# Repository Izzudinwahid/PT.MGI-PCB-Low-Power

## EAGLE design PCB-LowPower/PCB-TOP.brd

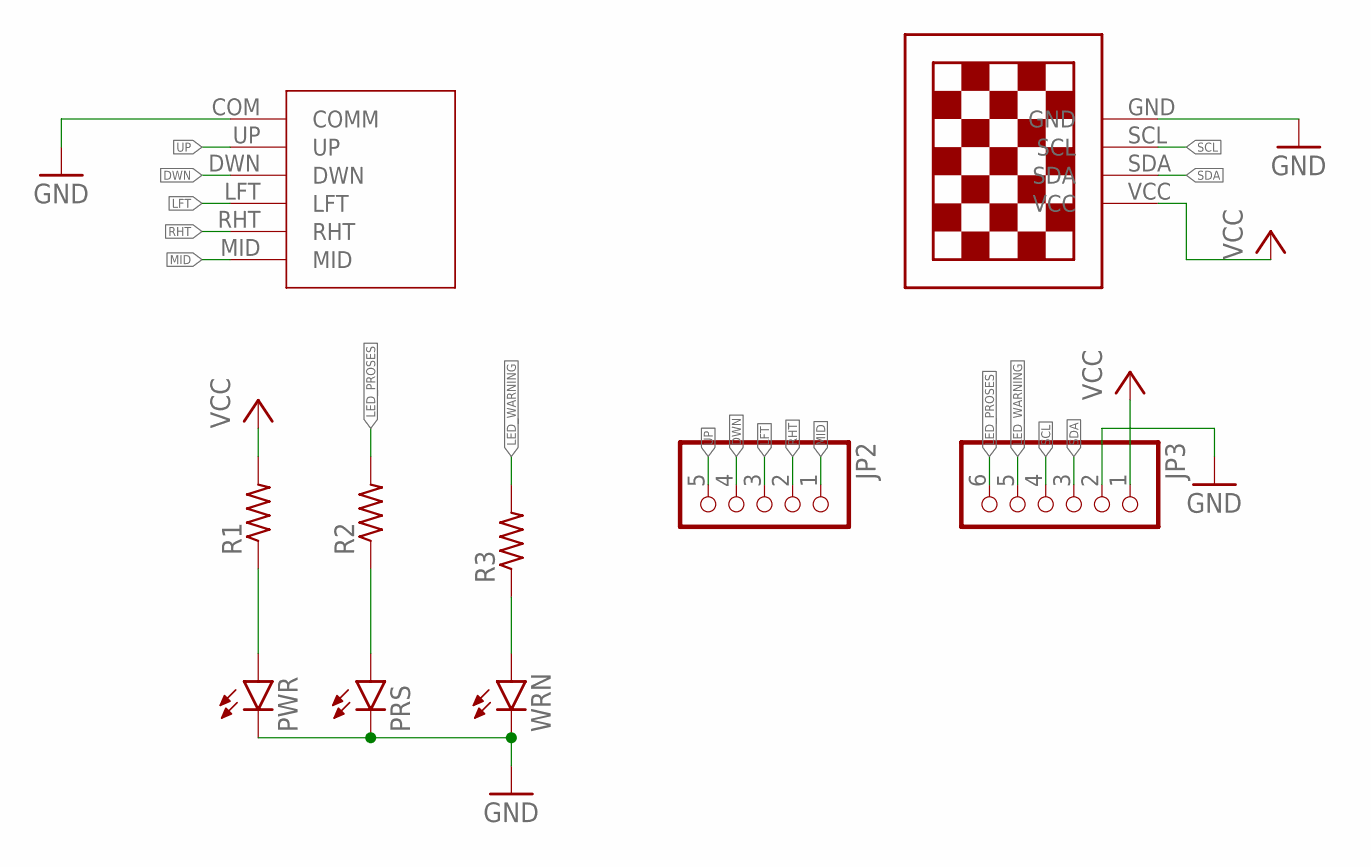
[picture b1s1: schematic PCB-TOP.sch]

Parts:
JP2: PINHD-1X5; 1X05
JP3: PINHD-1X6; 1X06
NAV-SWITCH6P1: NAV-SWITCH6P
PRS: TLLR4400; LED3MM
PWR: TLLR4400; LED3MM
R1, R2, R3: R-US_M0805; M0805
U$1: 13"OLED13"OLED; 1.3"OLED
WRN: TLLR4400; LED3MM

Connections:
DWN: JP2.4, NAV-SWITCH6P1.DWN
GND: JP3.2, NAV-SWITCH6P1.COM (COMM), PRS.K (C), PWR.K (C), U$1.GND, WRN.K (C)
LED_PROSES: JP3.6, R2.2
LED_WARNING: JP3.5, R3.2
LFT: JP2.3, NAV-SWITCH6P1.LFT
MID: JP2.1, NAV-SWITCH6P1.MID
unnamed: PWR.A, R1.1
unnamed: PRS.A, R2.1
unnamed: R3.1, WRN.A
RHT: JP2.2, NAV-SWITCH6P1.RHT
SCL: JP3.4, U$1.SCL
SDA: JP3.3, U$1.SDA
UP: JP2.5, NAV-SWITCH6P1.UP
VCC: JP3.1, R1.2, U$1.VCC

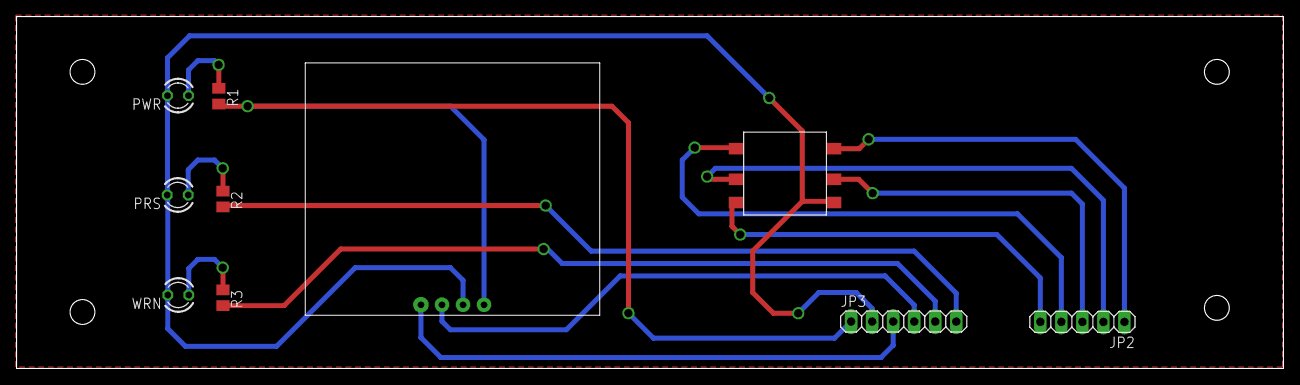
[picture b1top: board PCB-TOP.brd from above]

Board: 2 copper layers, 153.0 x 42.5 mm, 10 parts (0 on the bottom side), 14 nets.

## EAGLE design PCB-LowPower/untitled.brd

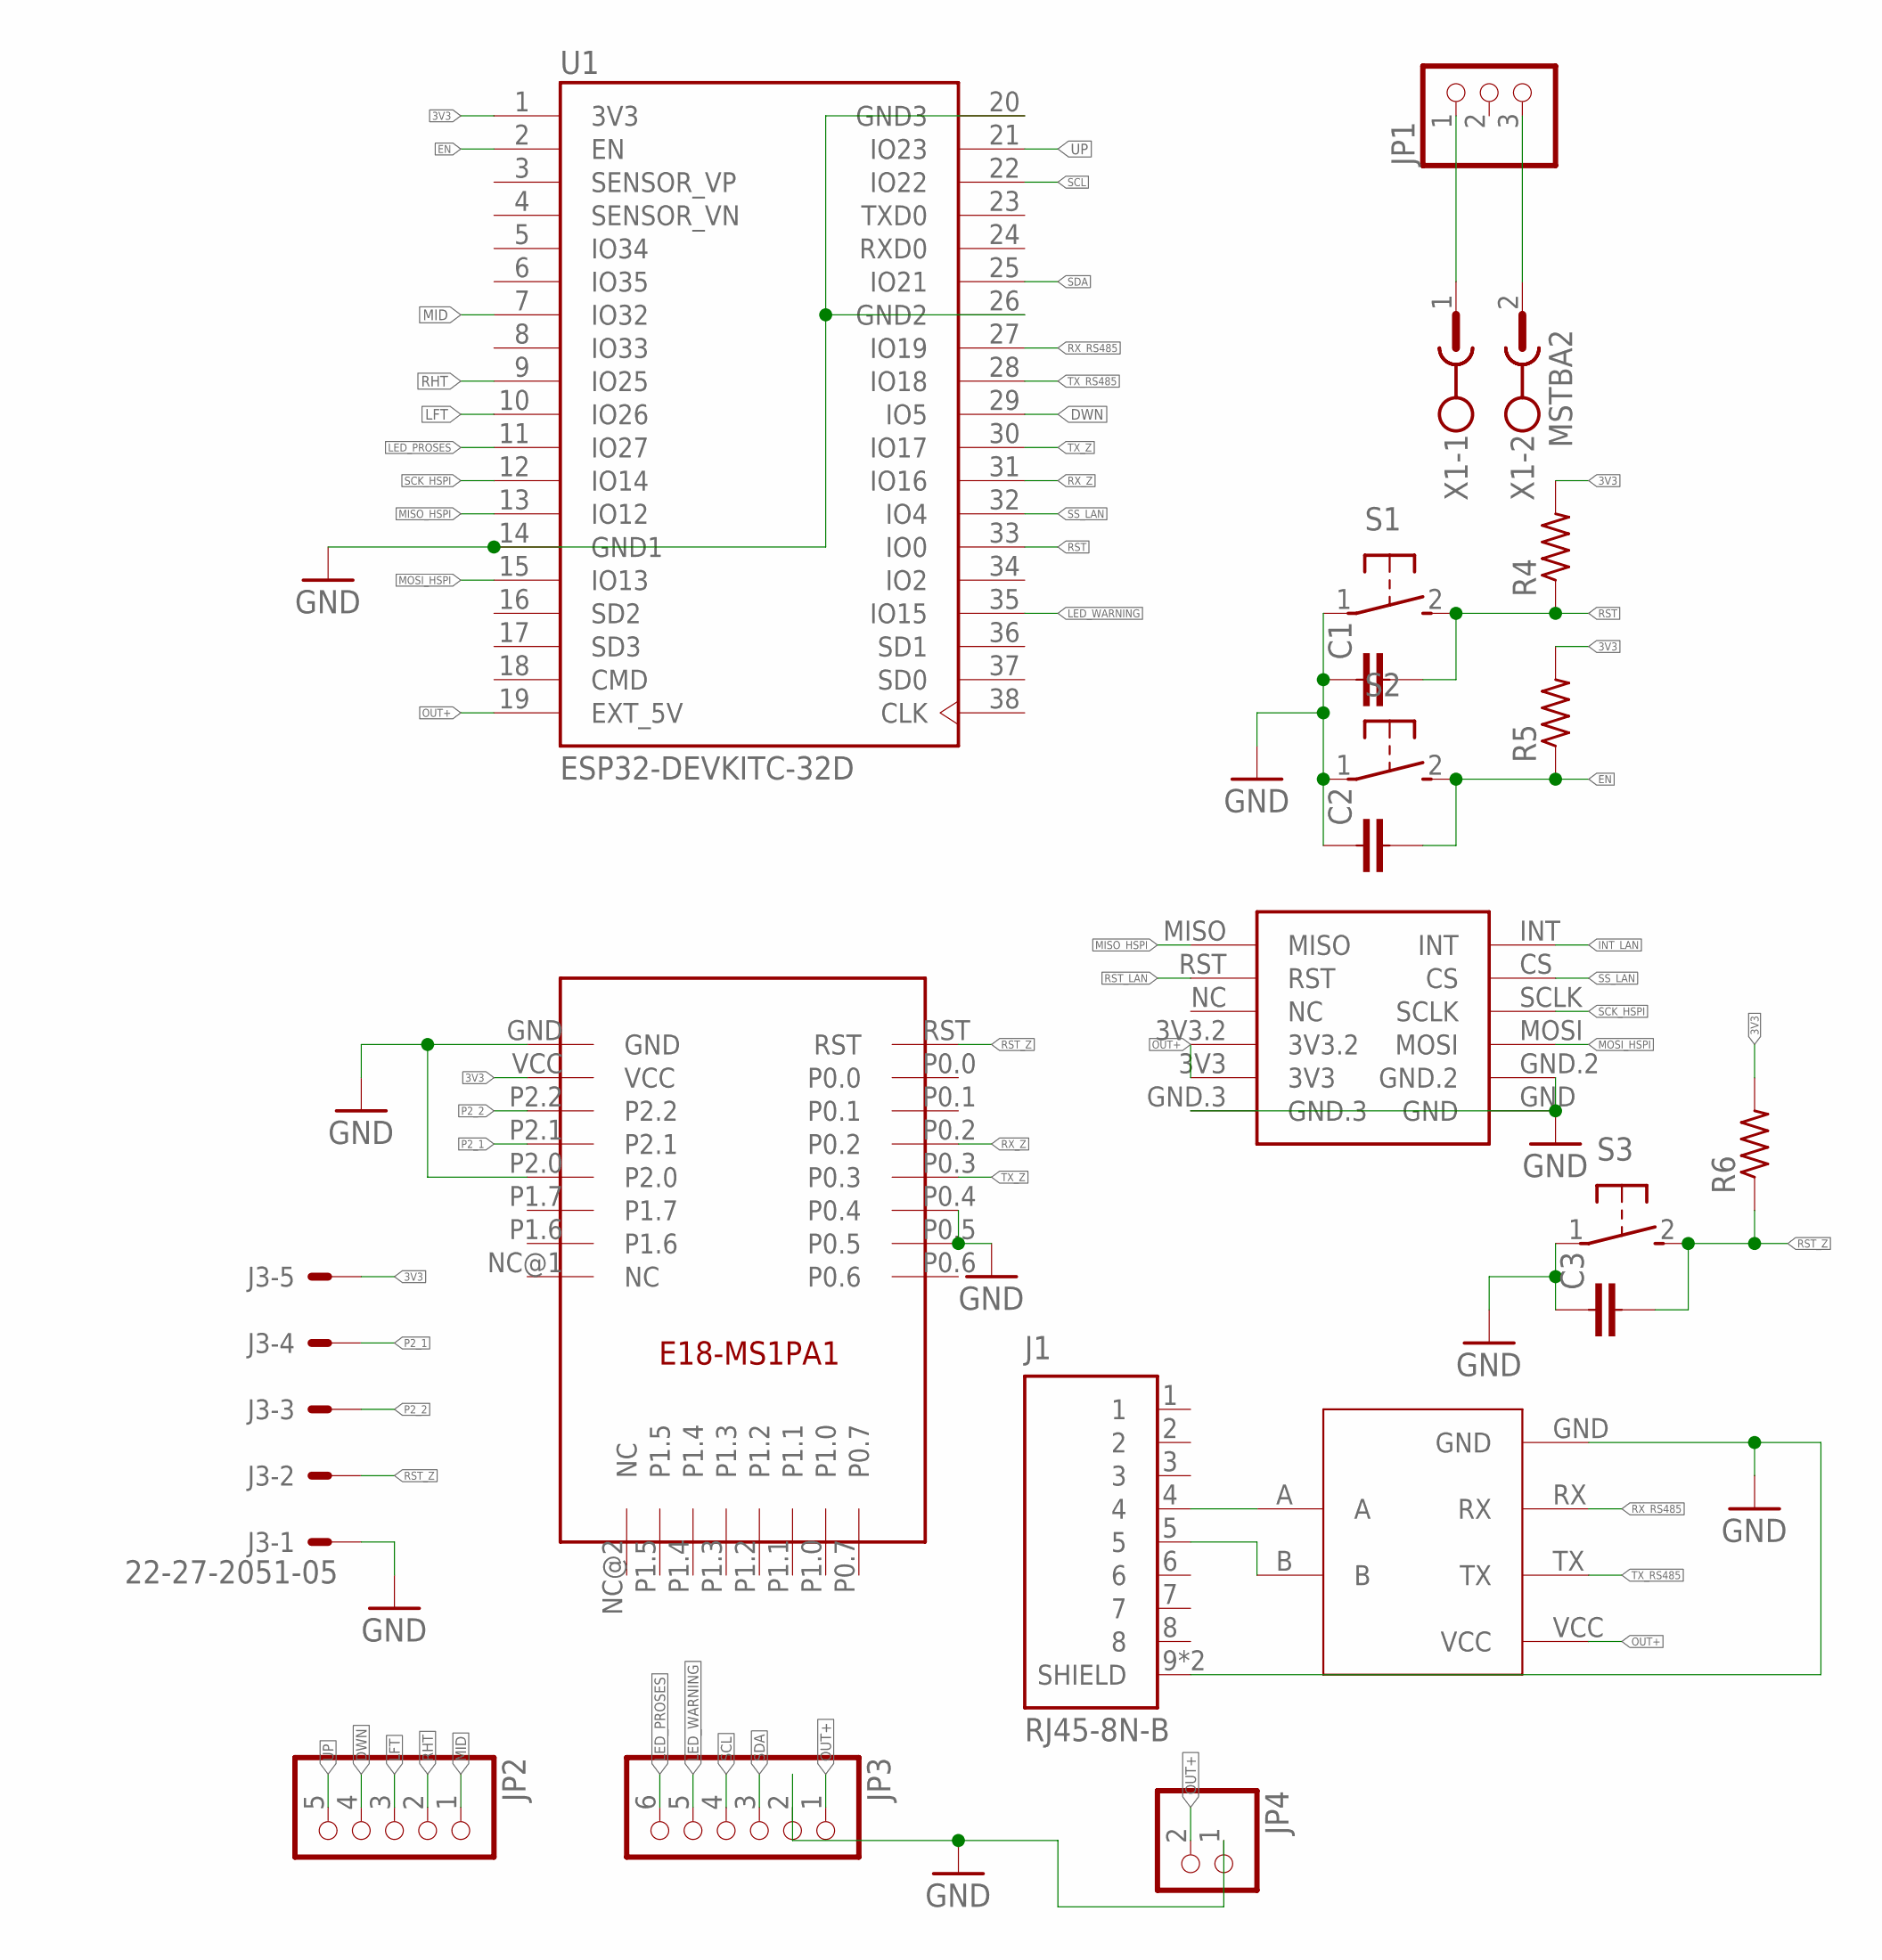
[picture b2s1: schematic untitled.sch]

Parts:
C1, C2, C3: C-EUC0805K; C0805K
J1: RJ45-8N-B; TE_RJ45-8N-B
J3: 22-27-2051-05; 6410-05
JP1: PINHD-1X3; 1X03
JP2: PINHD-1X5; 1X05
JP3: PINHD-1X6; 1X06
JP4: PINHD-1X2; 1X02
R4, R5, R6: R-US_M0805; M0805
S1, S2, S3: 31-XX; B3F-31XX
TTL-RS1: TTL-RS485
U1: ESP32-DEVKITC-32D; MODULE_ESP32-DEVKITC-32D
U$1: E18-MS1PA1IPX; E18-MS1PA1-IPX
U$2: MINI_W5500
X1: MSTBA2

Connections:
3V3: J3.5, R4.2, R5.2, R6.2, U1.1 (3V3), U$1.VCC
DWN: JP2.4, U1.29 (IO5)
EN: C2.2, R5.1, S2.2 (S), U1.2 (EN)
GND: C1.1, C2.1, C3.1, J1.9 (SHIELD), J1.10 (SHIELD), J3.1, JP3.2, JP4.1, S1.1, S2.1, S3.1, TTL-RS1.GND, U1.14 (GND1), U1.20 (GND3), U1.26 (GND2), U$1.GND, U$1.P0.4, U$1.P0.5, U$1.P2.0, U$2.GND, U$2.GND.2, U$2.GND.3
INT_LAN: U$2.INT
LED_PROSES: JP3.6, U1.11 (IO27)
LED_WARNING: JP3.5, U1.35 (IO15)
LFT: JP2.3, U1.10 (IO26)
MID: JP2.1, U1.7 (IO32)
MISO_HSPI: U1.13 (IO12), U$2.MISO
MOSI_HSPI: U1.15 (IO13), U$2.MOSI
unnamed: JP1.1, X1.1
unnamed: JP1.3, X1.2
unnamed: J1.4, TTL-RS1.A
unnamed: J1.5, TTL-RS1.B
OUT+: JP3.1, JP4.2, TTL-RS1.VCC, U1.19 (EXT_5V), U$2.3V3, U$2.3V3.2
P2_1: J3.4, U$1.P2.1
P2_2: J3.3, U$1.P2.2
RHT: JP2.2, U1.9 (IO25)
RST: C1.2, R4.1, S1.2 (S), U1.33 (IO0)
RST_LAN: U$2.RST
RST_Z: C3.2, J3.2, R6.1, S3.2 (S), U$1.RST
RX_RS485: TTL-RS1.RX, U1.27 (IO19)
RX_Z: U1.31 (IO16), U$1.P0.2
SCK_HSPI: U1.12 (IO14), U$2.SCLK
SCL: JP3.4, U1.22 (IO22)
SDA: JP3.3, U1.25 (IO21)
SS_LAN: U1.32 (IO4), U$2.CS
TX_RS485: TTL-RS1.TX, U1.28 (IO18)
TX_Z: U1.30 (IO17), U$1.P0.3
UP: JP2.5, U1.21 (IO23)

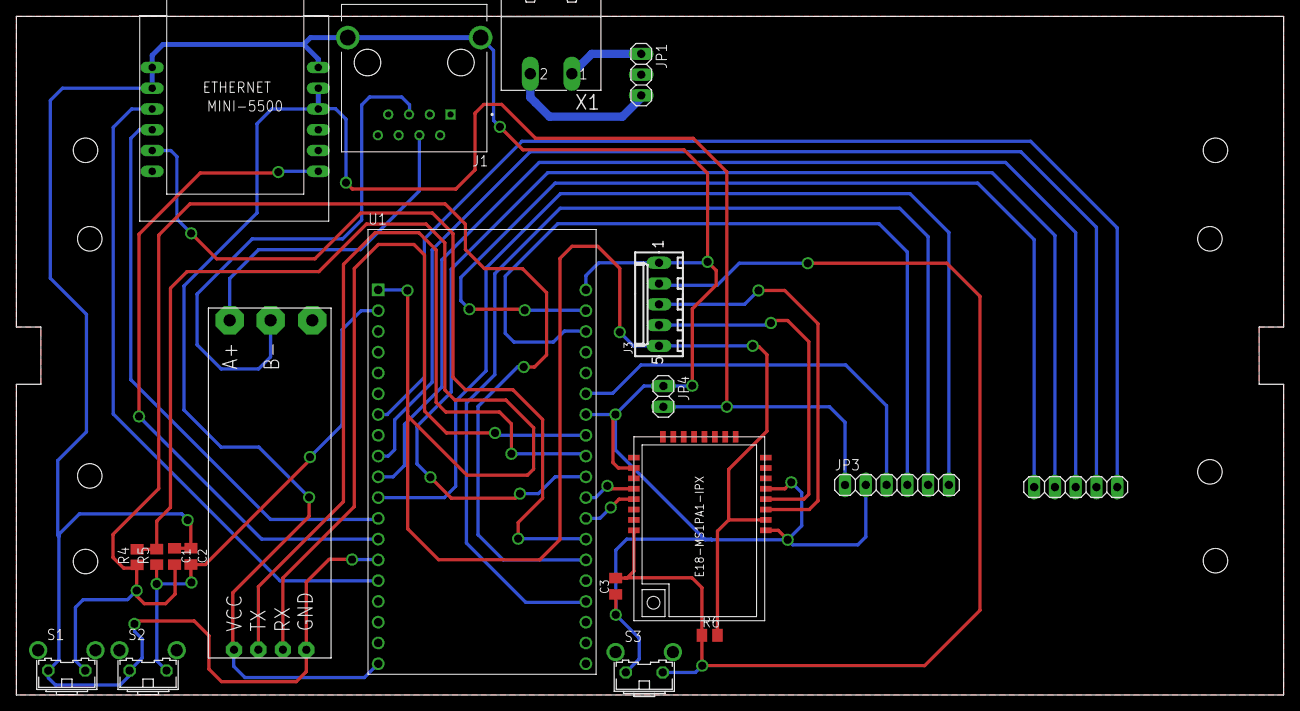
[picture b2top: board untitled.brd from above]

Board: 2 copper layers, 155.0 x 83.0 mm, 20 parts (0 on the bottom side), 29 nets.

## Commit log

2022-11-01 pcb low power
2022-11-02 revisi PCB
2022-11-03 menambahkan rangkaian PCB TOP
